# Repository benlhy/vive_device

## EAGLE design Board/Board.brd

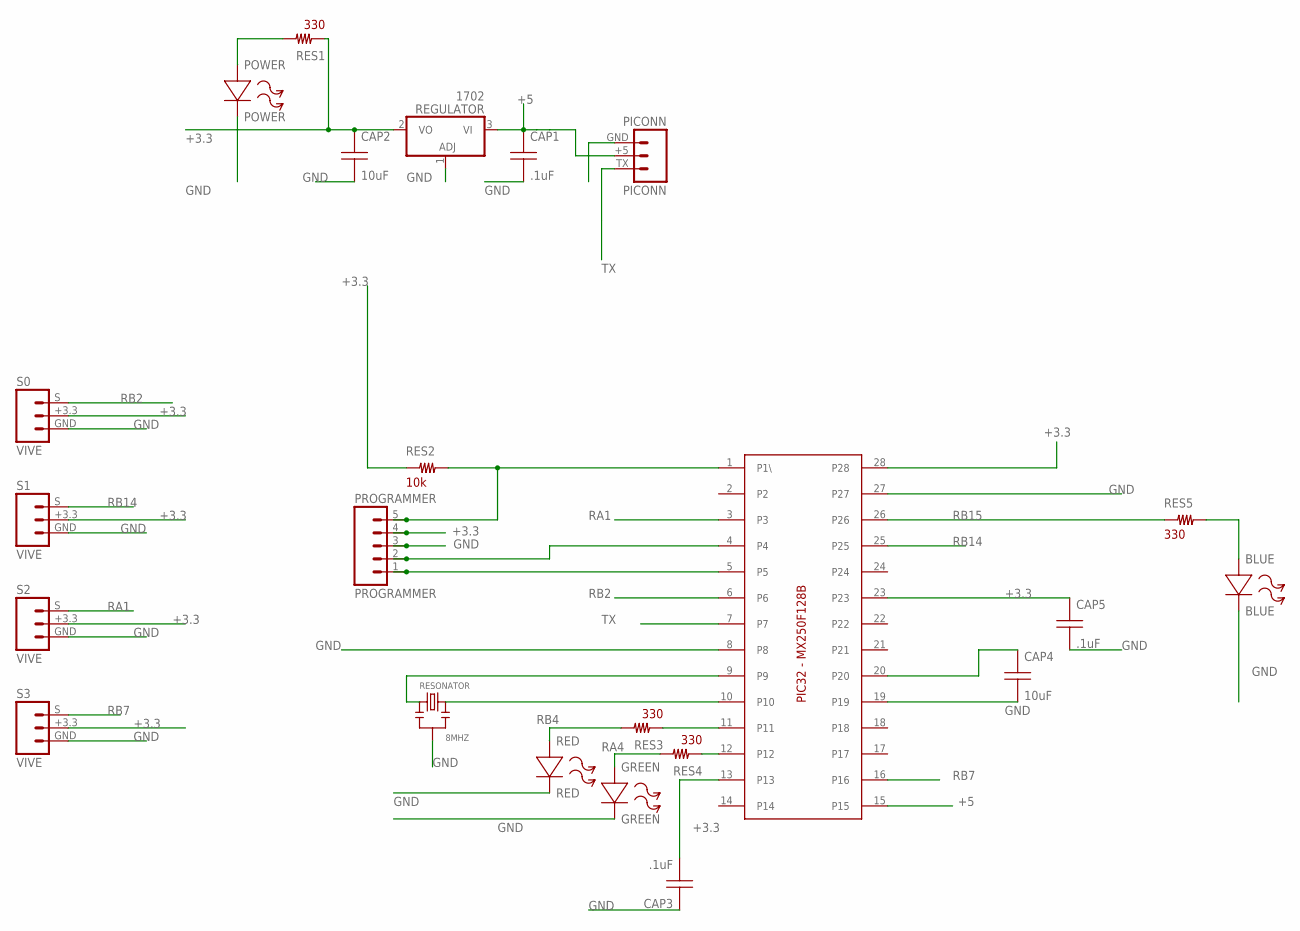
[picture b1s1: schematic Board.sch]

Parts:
1702: REGULATOR; REGULATOR3P
BLUE: BLUE; L0603
CAP1, CAP3, CAP5: .1uF; C0603
CAP2, CAP4: 10uF; C0805
GREEN: GREEN; L0603
PIC: PIC32-MX250F128BSSOP; PIC32SSOP
PICONN: PICONN
POWER: POWER; L0603
PROGRAMMER: PROGRAMMER; PROGRAMMER5P
RED: RED; L0603
RES1, RES3, RES4, RES5: 330; R0603
RES2: 10k; R0603
RESONATOR: 8MHZ; OSC
S0, S1, S2, S3: VIVE

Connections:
+3.3: 1702.2 (VO), CAP2.1 (A), CAP3.2 (B), CAP5.1 (A), PIC.13, PIC.23, PIC.28, PROGRAMMER.4, RES1.1, RES2.1, S0.+3.3, S1.+3.3, S2.+3.3, S3.+3.3
+5: 1702.3 (VI), CAP1.1 (A), PIC.15, PICONN.+5
GND: 1702.1 (ADJ), BLUE.2 (-), CAP1.2 (B), CAP2.2 (B), CAP3.1 (A), CAP4.2 (B), CAP5.2 (B), GREEN.2 (-), PIC.8, PIC.19, PIC.27, PICONN.GND, POWER.2 (-), PROGRAMMER.3, RED.2 (-), RESONATOR.2, S0.GND, S1.GND, S2.GND, S3.GND
unnamed: PIC.10, RESONATOR.3
unnamed: PIC.9, RESONATOR.1
unnamed: POWER.1 (+), RES1.2
unnamed: PIC.4, PROGRAMMER.2
unnamed: CAP4.1 (A), PIC.20
unnamed: PIC.12, RES4.1
unnamed: PIC.1 (P1\), PROGRAMMER.5, RES2.2
unnamed: PIC.11, RES3.1
unnamed: PIC.5, PROGRAMMER.1
unnamed: BLUE.1 (+), RES5.2
RA1: PIC.3, S2.S
RA4: GREEN.1 (+), RES4.2
RB2: PIC.6, S0.S
RB4: RED.1 (+), RES3.2
RB7: PIC.16, S3.S
RB14: PIC.25, S1.S
RB15: PIC.26, RES5.1
TX: PIC.7, PICONN.TX

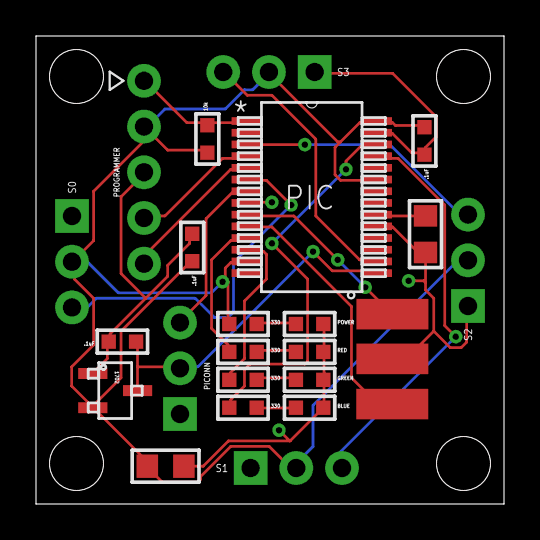
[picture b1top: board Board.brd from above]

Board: 2 copper layers, 26.0 x 26.0 mm, 23 parts (0 on the bottom side), 21 nets.

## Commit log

2018-04-06 vive_device
    First version
